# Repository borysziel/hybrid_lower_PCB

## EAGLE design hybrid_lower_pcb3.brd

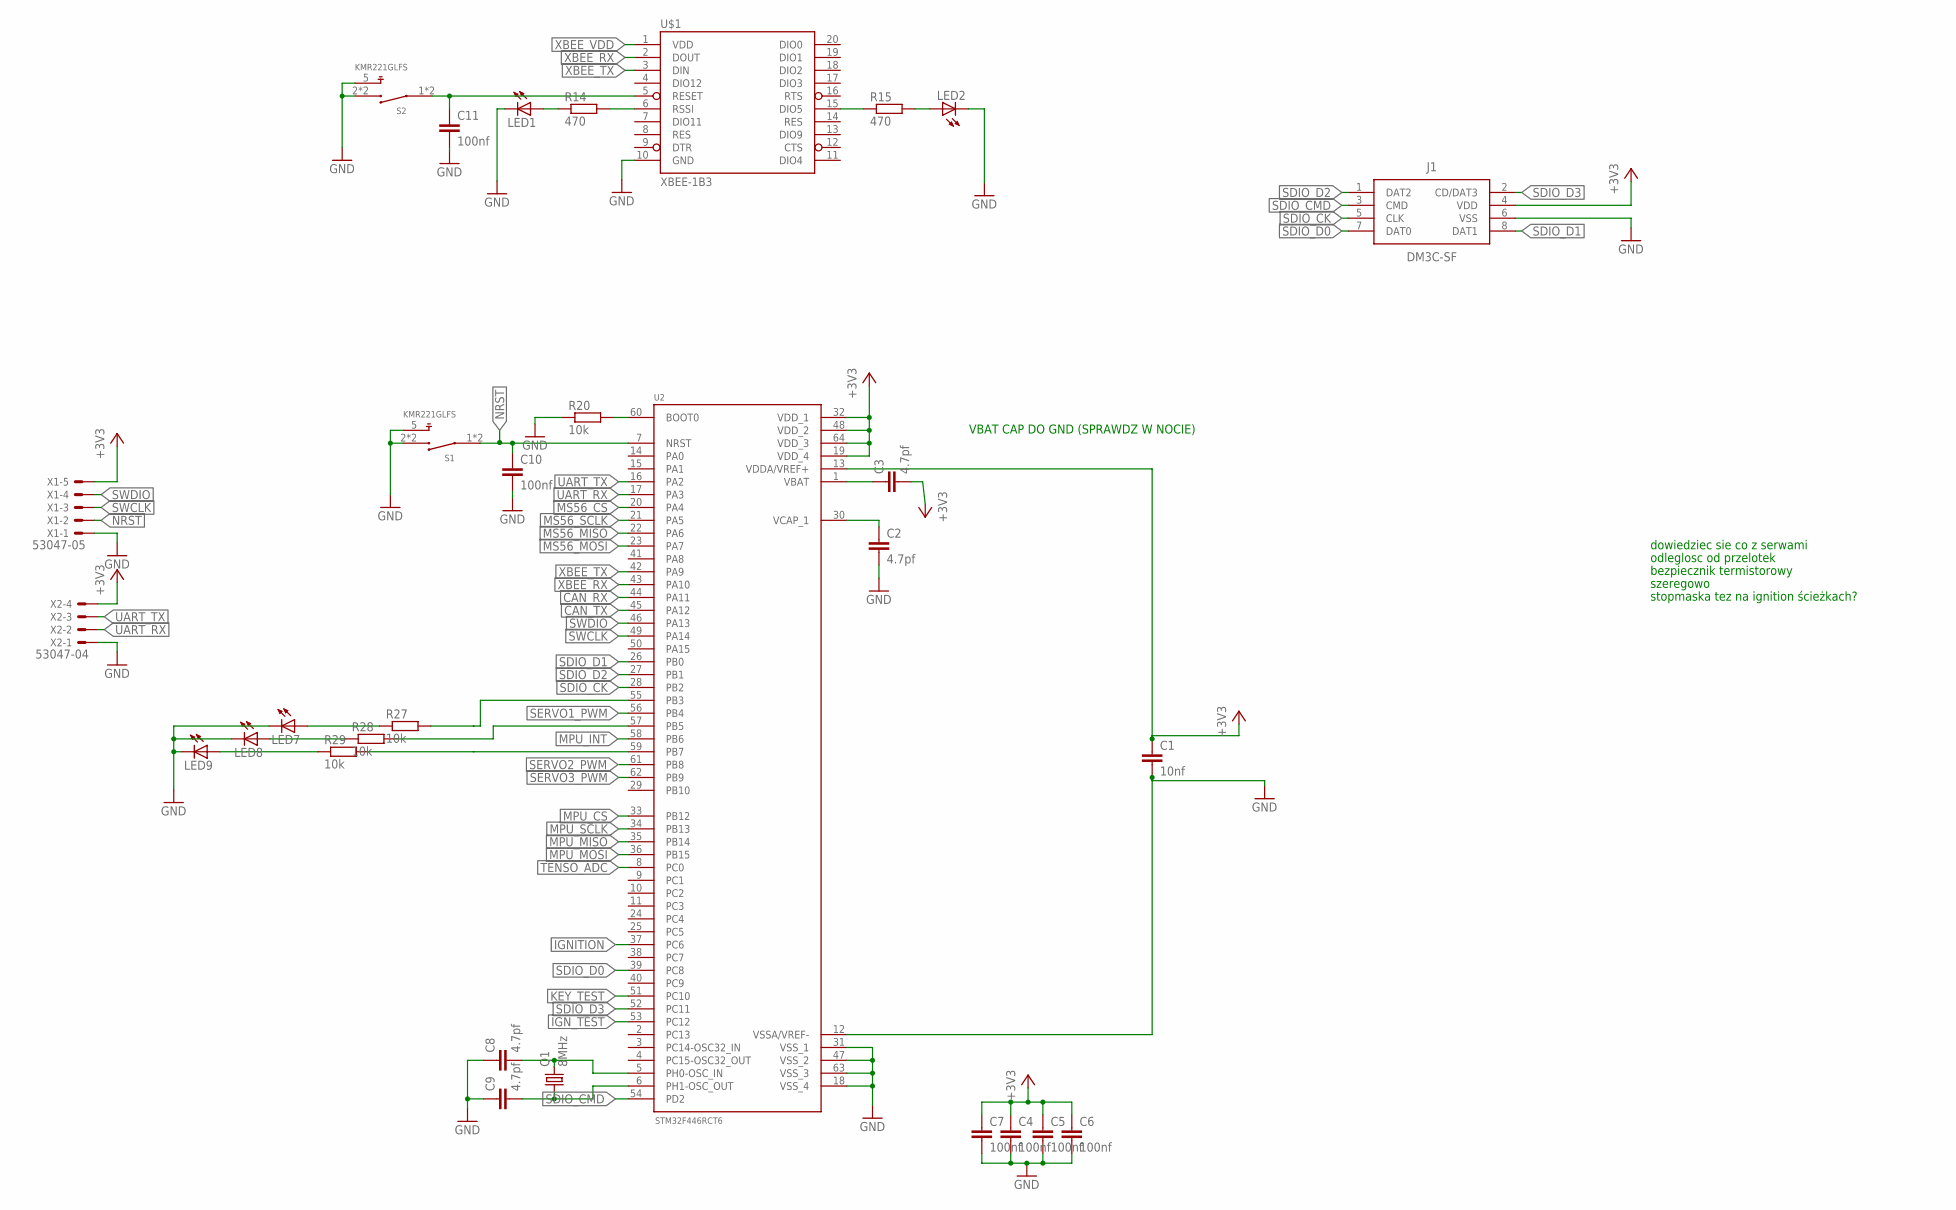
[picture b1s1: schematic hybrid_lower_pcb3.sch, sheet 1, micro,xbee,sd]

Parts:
C1: 10nf; C0603
C2, C3, C8, C9: 4.7pf; C0603
C4, C5, C6, C7, C10, C11: 100nf; C0603
J1: DM3C-SF
LED1, LED2, LED7, LED8, LED9: LED0603; LED-0603
Q1: 8MHz; CTS406
R14, R15: 470; R0603
R20, R27, R28, R29: 10k; R0603
S1, S2: KMR221GLFS; SW_KMR221GLFS
U2: STM32F446RCT6; QFP50P1200X1200X160-64N
U$1: XBEE-1B3; XBEE-SMD
X1: 53047-05
X2: 53047-04

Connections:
+3V3: C1.1, C3.2, C4.1, C5.1, C6.1, C7.1, J1.4 (VDD), U2.13 (VDDA/VREF+), U2.19 (VDD_4), U2.32 (VDD_1), U2.48 (VDD_2), U2.64 (VDD_3), X1.5, X2.4; also elsewhere on the board
CAN_RX: U2.44 (PA11); also elsewhere on the board
CAN_TX: U2.45 (PA12); also elsewhere on the board
DUPA: C11.1, S2.1, S2.4 (1), U$1.5 (RESET)
GND: C1.2, C2.2, C4.2, C5.2, C6.2, C7.2, C8.1, C9.1, C10.2, C11.2, J1.6 (VSS), LED1.C, LED2.C, LED7.C, LED8.C, LED9.C, R20.1, S1.2 (3), S1.3, S1.5, S2.2 (3), S2.3, S2.5, U2.12 (VSSA/VREF-), U2.18 (VSS_4), U2.31 (VSS_1), U2.47 (VSS_2), U2.63 (VSS_3), U$1.10 (GND), X1.1, X2.1; also elsewhere on the board
IGNITION: U2.37 (PC6); also elsewhere on the board
IGN_TEST: U2.53 (PC12); also elsewhere on the board
KEY_TEST: U2.51 (PC10); also elsewhere on the board
MPU_CS: U2.33 (PB12); also elsewhere on the board
MPU_INT: U2.58 (PB6); also elsewhere on the board
MPU_MISO: U2.35 (PB14); also elsewhere on the board
MPU_MOSI: U2.36 (PB15); also elsewhere on the board
MPU_SCLK: U2.34 (PB13); also elsewhere on the board
MS56_CS: U2.20 (PA4); also elsewhere on the board
MS56_MISO: U2.22 (PA6); also elsewhere on the board
MS56_MOSI: U2.23 (PA7); also elsewhere on the board
MS56_SCLK: U2.21 (PA5); also elsewhere on the board
unnamed: C2.1, U2.30 (VCAP_1)
unnamed: C3.1, U2.1 (VBAT)
unnamed: LED1.A, R14.1
unnamed: C8.2, Q1.3 (2), U2.5 (PH0-OSC_IN)
unnamed: C9.2, Q1.1, U2.6 (PH1-OSC_OUT)
unnamed: LED2.A, R15.2
unnamed: R14.2, U$1.6 (RSSI)
unnamed: R15.1, U$1.15 (DIO5)
unnamed: R20.2, U2.60 (BOOT0)
unnamed: R27.2, U2.55 (PB3)
unnamed: R28.2, U2.57 (PB5)
unnamed: R29.2, U2.59 (PB7)
unnamed: LED7.A, R27.1
unnamed: LED8.A, R28.1
unnamed: LED9.A, R29.1
NRST: C10.1, S1.1, S1.4 (1), U2.7 (NRST), X1.2
SDIO_CK: J1.5 (CLK), U2.28 (PB2)
SDIO_CMD: J1.3 (CMD), U2.54 (PD2)
SDIO_D0: J1.7 (DAT0), U2.39 (PC8)
SDIO_D1: J1.8 (DAT1), U2.26 (PB0)
SDIO_D2: J1.1 (DAT2), U2.27 (PB1)
SDIO_D3: J1.2 (CD/DAT3), U2.52 (PC11)
SERVO1_PWM: U2.56 (PB4)
SERVO2_PWM: U2.61 (PB8); also elsewhere on the board
SERVO3_PWM: U2.62 (PB9); also elsewhere on the board
SWCLK: U2.49 (PA14), X1.3
SWDIO: U2.46 (PA13), X1.4
TENSO_ADC: U2.8 (PC0); also elsewhere on the board
UART_RX: U2.17 (PA3), X2.2
UART_TX: U2.16 (PA2), X2.3
XBEE_RX: U2.43 (PA10), U$1.2 (DOUT)
XBEE_TX: U2.42 (PA9), U$1.3 (DIN)
XBEE_VDD: U$1.1 (VDD); also elsewhere on the board

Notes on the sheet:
dowiedziec sie co z serwami
odleglosc od przelotek
bezpiecznik termistorowy
szeregowo
stopmaska tez na ignition ścieżkach?
VBAT CAP DO GND (SPRAWDZ W NOCIE)

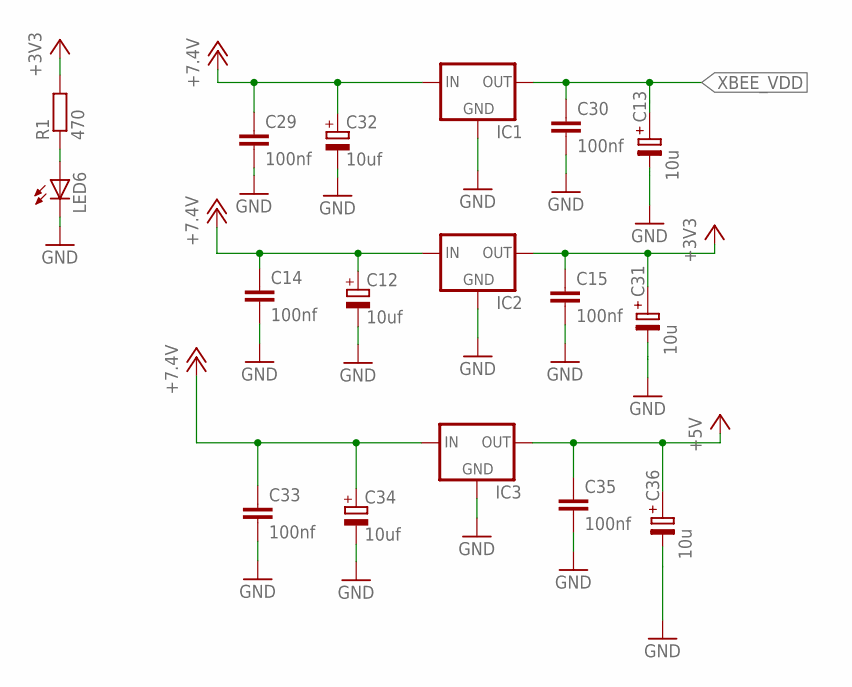
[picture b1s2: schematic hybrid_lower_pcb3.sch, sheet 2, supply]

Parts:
C12, C32, C34: 10uf; SANYO-OSCON_SMD_B6
C13, C31, C36: 10u; TE-B-3528
C14, C15, C29, C30, C33, C35: 100nf; C0603
IC1, IC2, IC3: LM1117; SOT223
LED6: LED0603; LED-0603
R1: 470; R0603

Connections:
+3V3: C15.1, C31.+, IC2.2 (OUT), R1.2; also elsewhere on the board
+5V: C35.1, C36.+, IC3.2 (OUT); also elsewhere on the board
+12V: C12.+, C14.1, C29.1, C32.+, C33.1, C34.+, IC1.3 (IN), IC2.3 (IN), IC3.3 (IN); also elsewhere on the board
GND: C12.-, C13.-, C14.2, C15.2, C29.2, C30.2, C31.-, C32.-, C33.2, C34.-, C35.2, C36.-, IC1.1 (GND), IC2.1 (GND), IC3.1 (GND), LED6.C; also elsewhere on the board
unnamed: LED6.A, R1.1
XBEE_VDD: C13.+, C30.1, IC1.2 (OUT); also elsewhere on the board

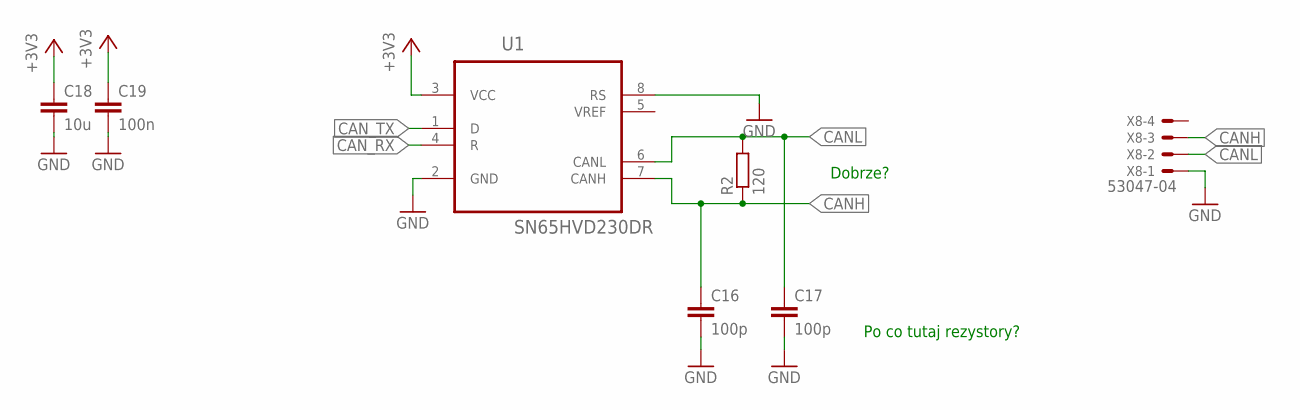
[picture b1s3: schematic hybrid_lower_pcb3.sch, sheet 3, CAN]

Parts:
C16, C17: 100p; C0603
C18: 10u; C0603
C19: 100n; C0603
R2: 120; R0603
U1: SN65HVD230DR; SOIC127P600X175-8N
X8: 53047-04

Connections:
+3V3: C18.1, C19.1, U1.3 (VCC); also elsewhere on the board
CANH: C16.1, R2.1, U1.7 (CANH), X8.3; also elsewhere on the board
CANL: C17.1, R2.2, U1.6 (CANL), X8.2; also elsewhere on the board
CAN_RX: U1.4 (R); also elsewhere on the board
CAN_TX: U1.1 (D); also elsewhere on the board
GND: C16.2, C17.2, C18.2, C19.2, U1.2 (GND), U1.8 (RS), X8.1; also elsewhere on the board

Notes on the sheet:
Po co tutaj rezystory?
Dobrze?

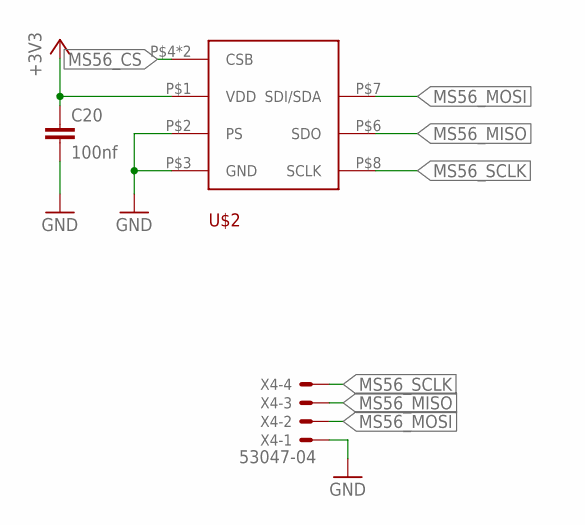
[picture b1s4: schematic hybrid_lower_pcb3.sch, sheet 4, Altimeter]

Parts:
C20: 100nf; C0603
U$2: MS56XX
X4: 53047-04

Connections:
+3V3: C20.1, U$2.P$1 (VDD); also elsewhere on the board
GND: C20.2, U$2.P$2 (PS), U$2.P$3 (GND), X4.1; also elsewhere on the board
MS56_CS: U$2.P$4 (CSB), U$2.P$5 (CSB); also elsewhere on the board
MS56_MISO: U$2.P$6 (SDO), X4.3; also elsewhere on the board
MS56_MOSI: U$2.P$7 (SDI/SDA), X4.2; also elsewhere on the board
MS56_SCLK: U$2.P$8 (SCLK), X4.4; also elsewhere on the board

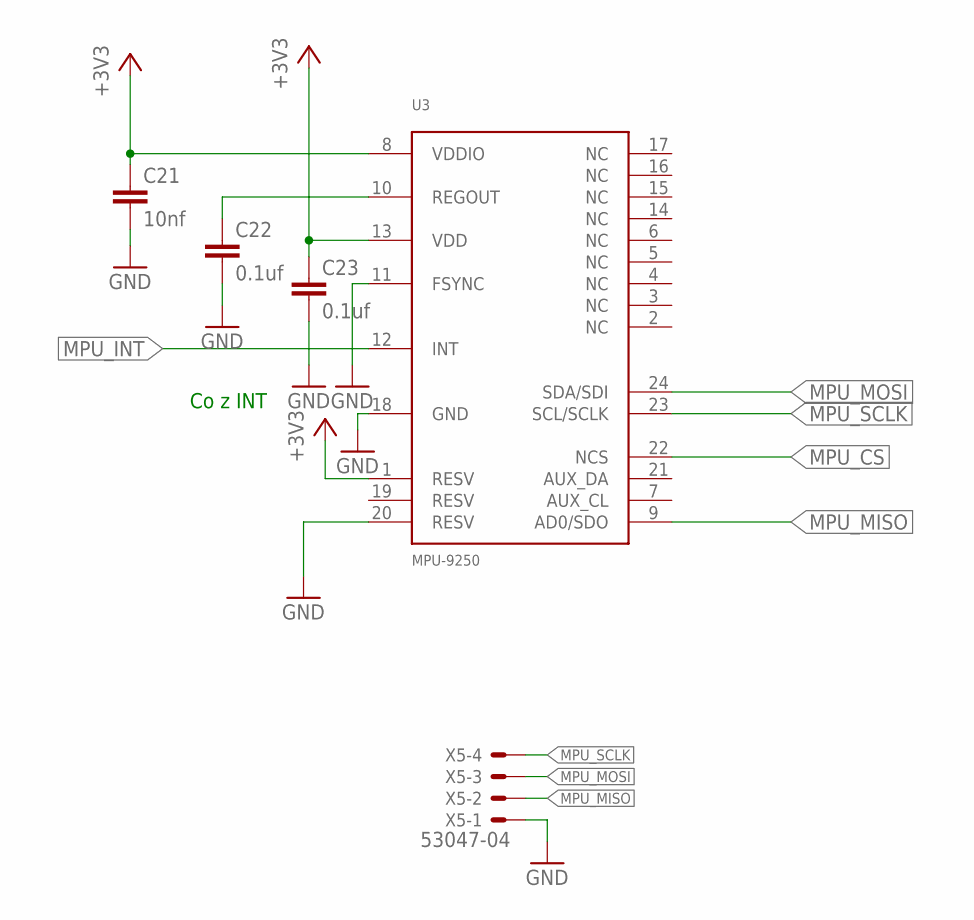
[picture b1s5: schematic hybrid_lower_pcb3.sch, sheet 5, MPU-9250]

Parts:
C21: 10nf; C0603
C22, C23: 0.1uf; C0603
U3: MPU-9250
X5: 53047-04

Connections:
+3V3: C21.1, C23.1, U3.1 (RESV), U3.8 (VDDIO), U3.13 (VDD); also elsewhere on the board
GND: C21.2, C22.2, C23.2, U3.11 (FSYNC), U3.18 (GND), U3.20 (RESV), X5.1; also elsewhere on the board
MPU_CS: U3.22 (NCS); also elsewhere on the board
MPU_INT: U3.12 (INT); also elsewhere on the board
MPU_MISO: U3.9 (AD0/SDO), X5.2; also elsewhere on the board
MPU_MOSI: U3.24 (SDA/SDI), X5.3; also elsewhere on the board
MPU_SCLK: U3.23 (SCL/SCLK), X5.4; also elsewhere on the board
unnamed: C22.1, U3.10 (REGOUT)

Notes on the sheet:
Co z INT

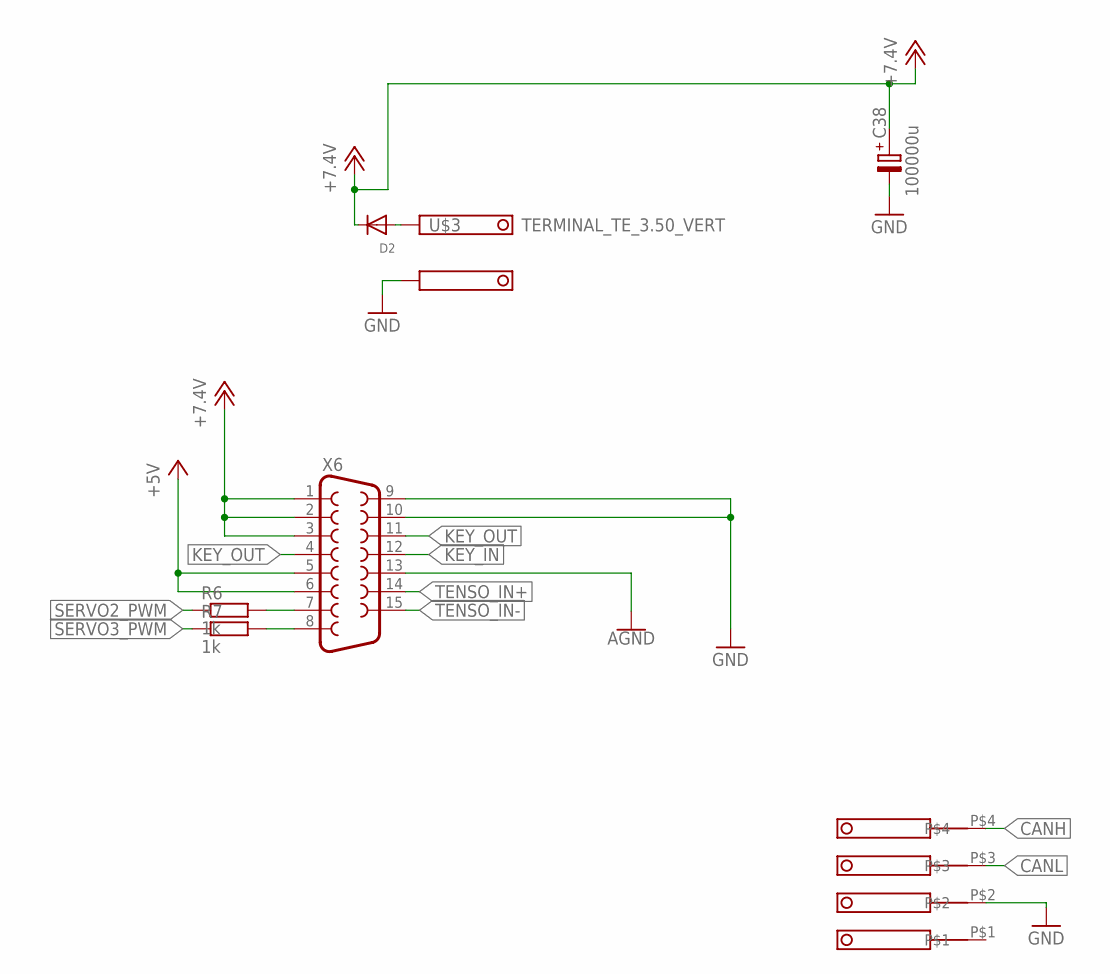
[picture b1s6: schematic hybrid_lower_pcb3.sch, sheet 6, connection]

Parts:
C38: 100000u; TE-B-3528
D2: DIODESOD-523; SOD-523
R6, R7: 1k; R0603
U$3: TERMINAL_TE_3.50_VERT; TE_3.5_TERMINAL_VERT
U$10: 39505-1005
X6: F15VP

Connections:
+5V: X6.5, X6.6; also elsewhere on the board
+12V: C38.+, D2.K (C), X6.1, X6.2, X6.3; also elsewhere on the board
AGND: X6.13; also elsewhere on the board
CANH: U$10.P$4; also elsewhere on the board
CANL: U$10.P$3; also elsewhere on the board
GND: C38.-, U$3.P$2 (K1), U$10.P$2, X6.9, X6.10; also elsewhere on the board
KEY_IN: X6.12; also elsewhere on the board
KEY_OUT: X6.4, X6.11; also elsewhere on the board
unnamed: R6.2, X6.7
unnamed: R7.2, X6.8
unnamed: D2.A, U$3.P$1 (K)
SERVO2_PWM: R6.1; also elsewhere on the board
SERVO3_PWM: R7.1; also elsewhere on the board
TENSO_IN+: X6.14; also elsewhere on the board
TENSO_IN-: X6.15; also elsewhere on the board

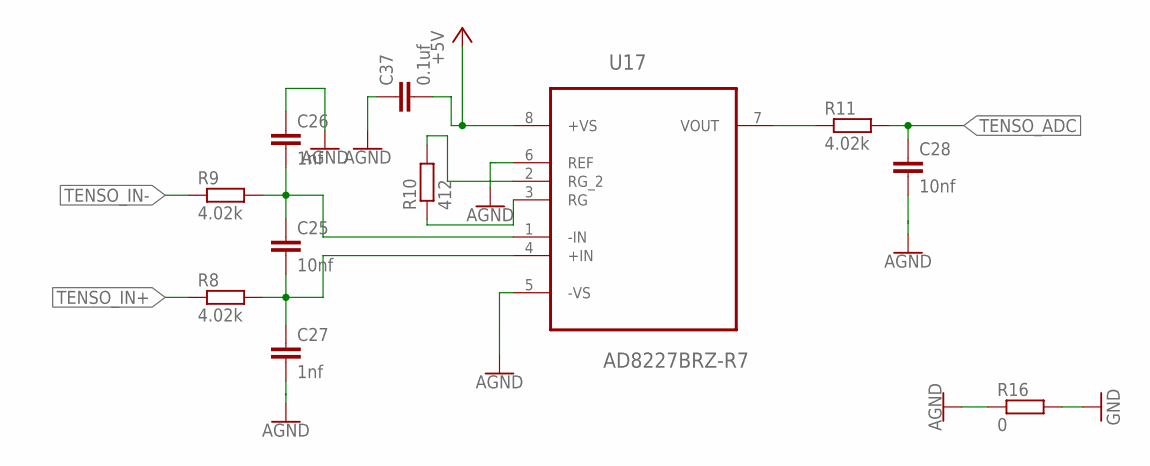
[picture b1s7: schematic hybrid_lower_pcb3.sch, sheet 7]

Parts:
C25, C28: 10nf; C0603
C26, C27: 1nf; C0603
C37: 0.1uf; C0603
R8, R9, R11: 4.02k; R0603
R10: 412; R0805
R16: 0; R0603
U17: AD8227BRZ-R7; SOIC127P600X175-8N

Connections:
+5V: C37.2, U17.8 (+VS); also elsewhere on the board
AGND: C26.1, C27.2, C28.2, C37.1, R16.1, U17.5 (-VS), U17.6 (REF); also elsewhere on the board
GND: R16.2; also elsewhere on the board
unnamed: C25.1, C26.2, R9.2, U17.1 (-IN)
unnamed: C25.2, C27.1, R8.2, U17.4 (+IN)
unnamed: R10.1, U17.3 (RG)
unnamed: R10.2, U17.2 (RG_2)
unnamed: R11.1, U17.7 (VOUT)
TENSO_ADC: C28.1, R11.2; also elsewhere on the board
TENSO_IN+: R8.1; also elsewhere on the board
TENSO_IN-: R9.1; also elsewhere on the board

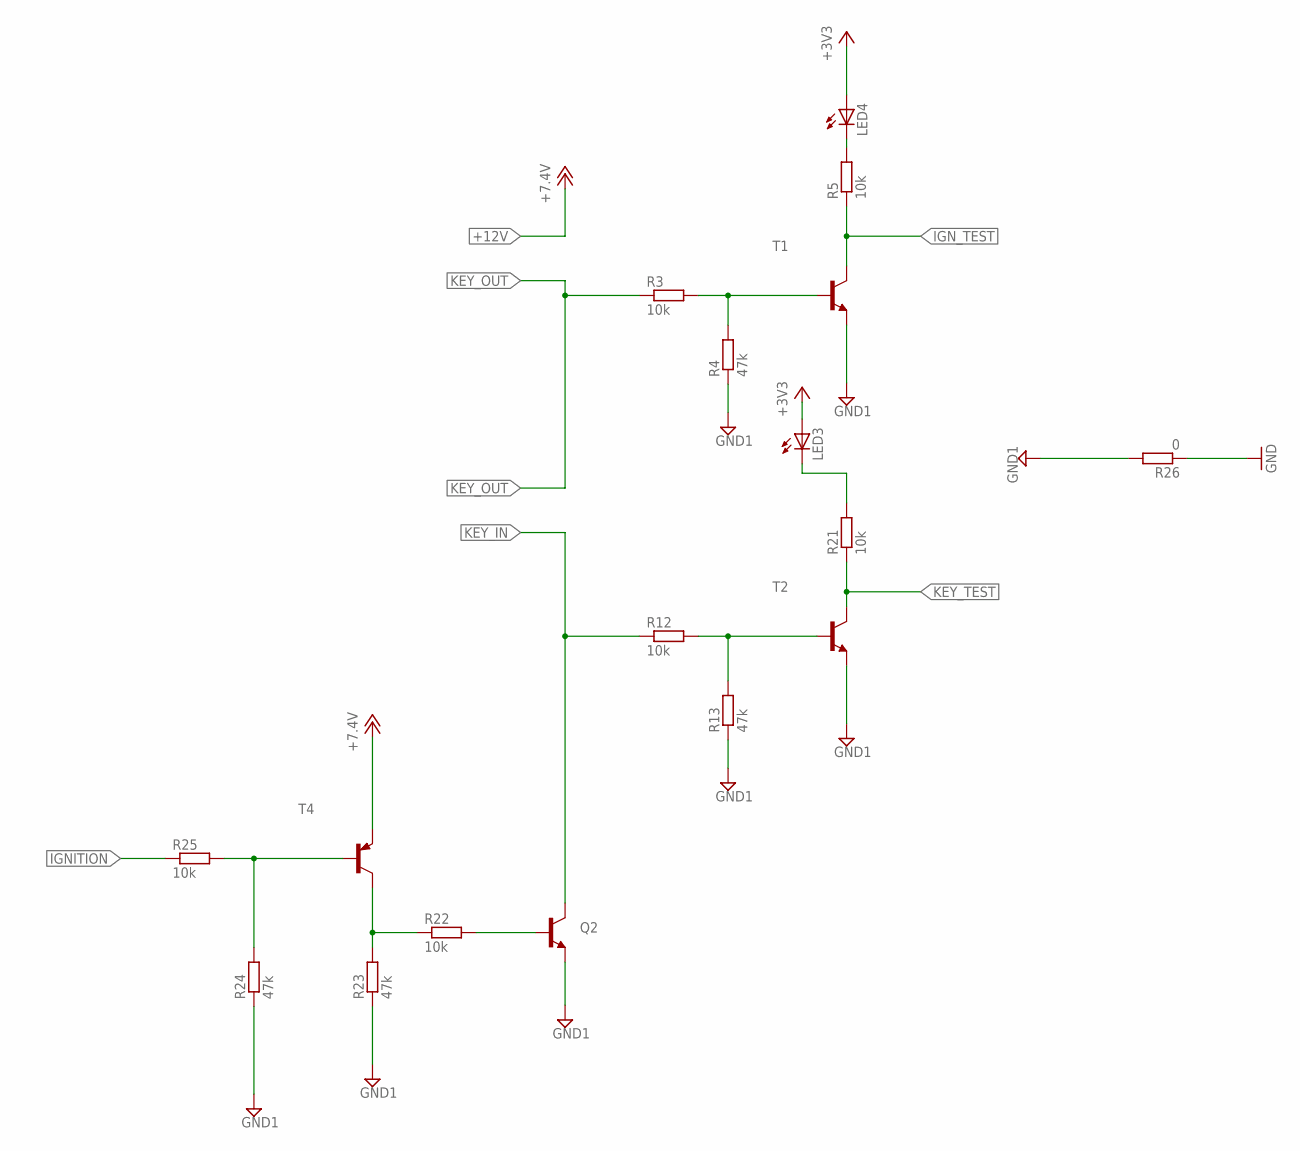
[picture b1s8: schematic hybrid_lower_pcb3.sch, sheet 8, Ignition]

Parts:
LED3, LED4: LED0603; LED-0603
Q2: TRANSISTOR_NPNSOT23-3; SOT23-3
R3, R5, R12, R21, R22, R25: 10k; R0603
R4, R13, R23, R24: 47k; R0603
R26: 0; R0603
T1, T2: BCW81-NPN-SOT23-BEC; SOT23-BEC
T4: BC807-16-PNP-SOT23-BEC; SOT23-BEC

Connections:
+3V3: LED3.A, LED4.A; also elsewhere on the board
+12V: T4.E; also elsewhere on the board
GND: R26.1; also elsewhere on the board
GND1: Q2.2 (E), R4.1, R13.1, R23.1, R24.1, R26.2, T1.E, T2.E
IGNITION: R25.1; also elsewhere on the board
IGN_TEST: R5.1, T1.C; also elsewhere on the board
KEY_IN: Q2.3 (C), R12.1; also elsewhere on the board
KEY_OUT: R3.1; also elsewhere on the board
KEY_TEST: R21.1, T2.C; also elsewhere on the board
unnamed: R3.2, R4.2, T1.B
unnamed: R12.2, R13.2, T2.B
unnamed: LED4.C, R5.2
unnamed: LED3.C, R21.2
unnamed: Q2.1 (B), R22.2
unnamed: R22.1, R23.2, T4.C
unnamed: R24.2, R25.2, T4.B

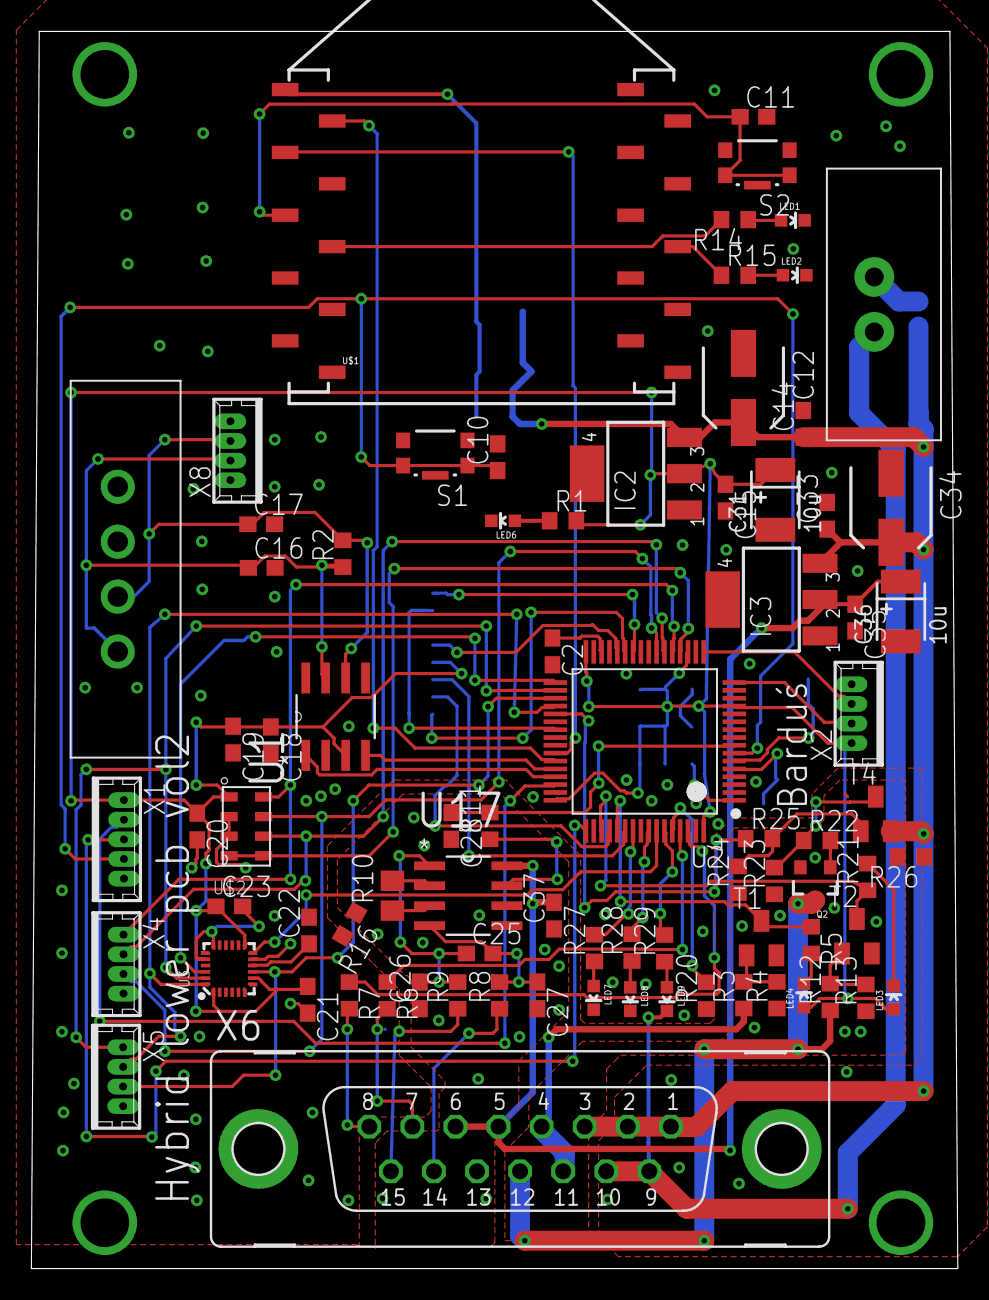
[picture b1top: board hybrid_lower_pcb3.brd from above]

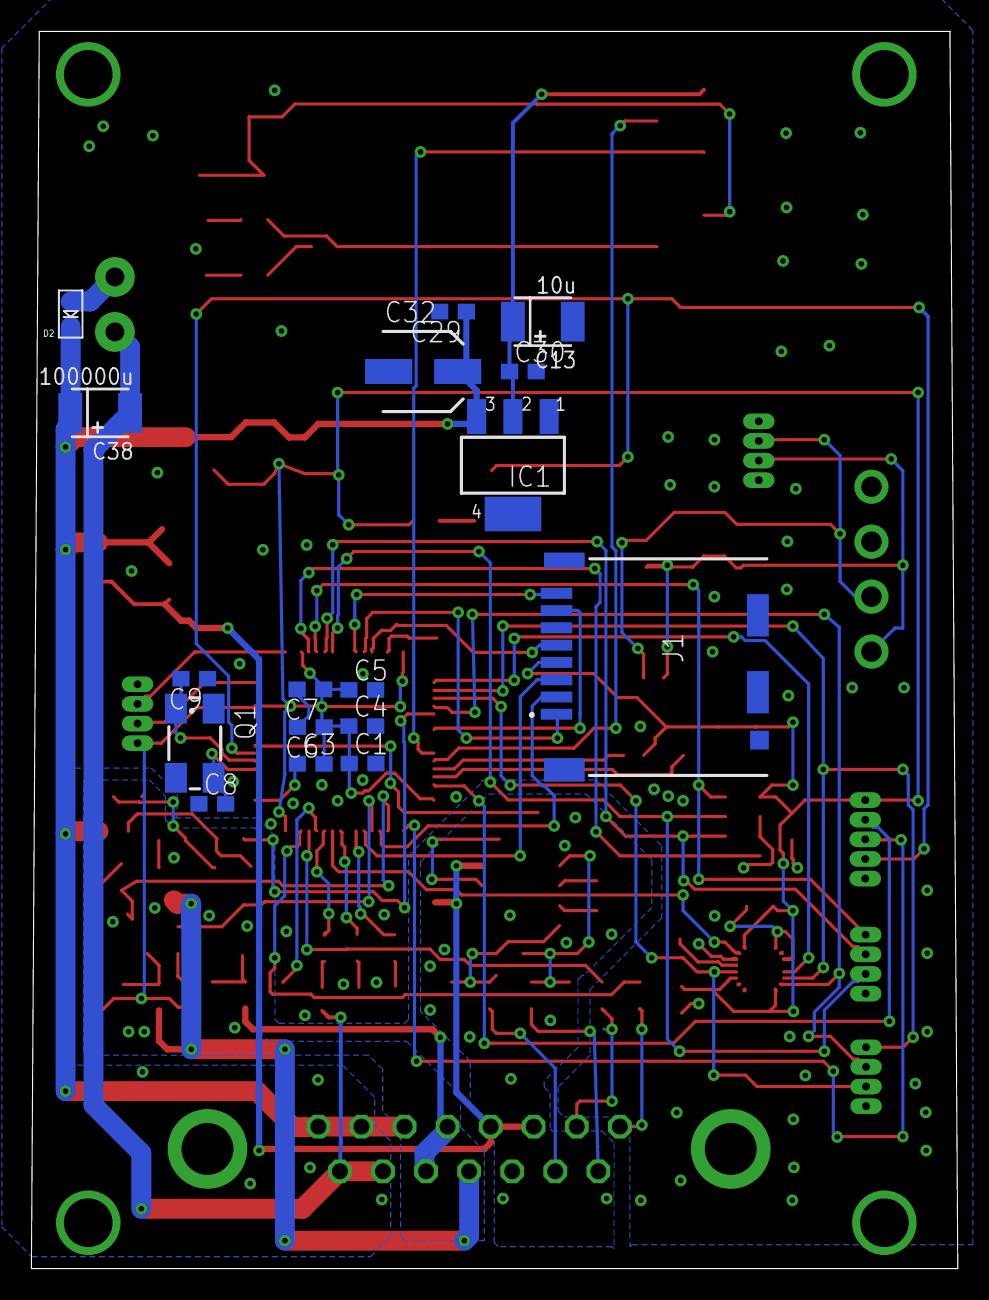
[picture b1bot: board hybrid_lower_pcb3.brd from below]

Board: 2 copper layers, 59.0 x 78.8 mm, 98 parts (17 on the bottom side), 76 nets.

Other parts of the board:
U$15: LOGO

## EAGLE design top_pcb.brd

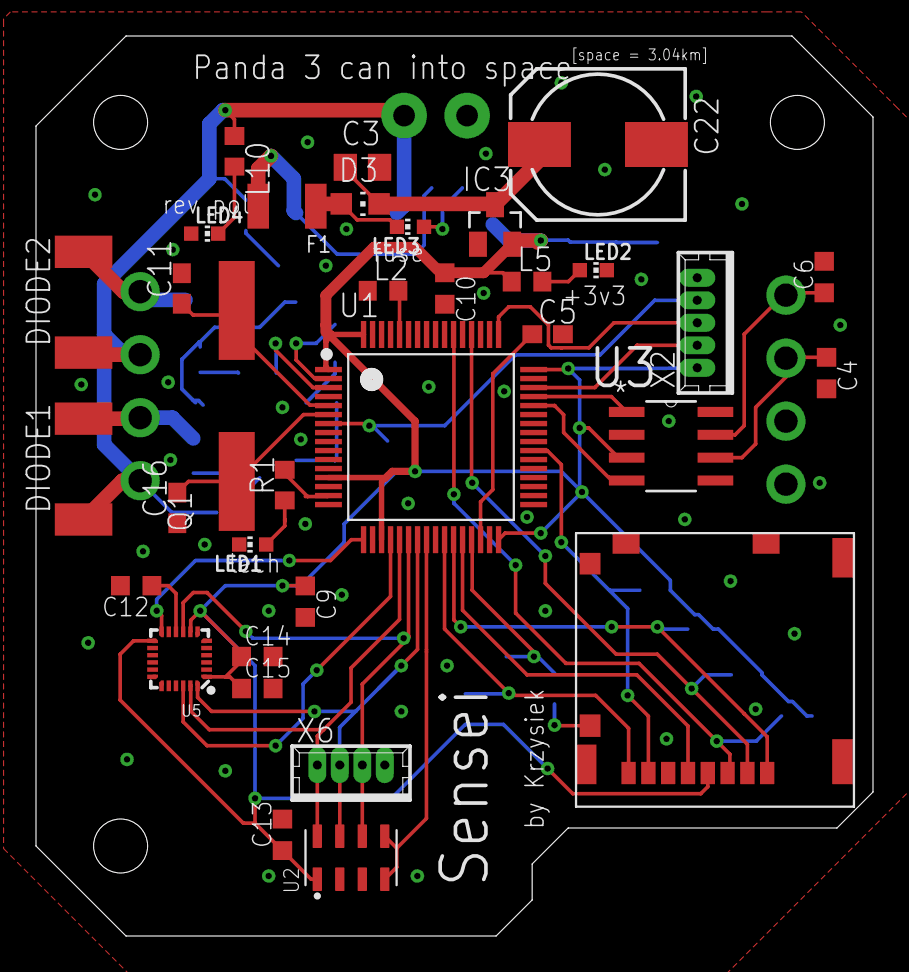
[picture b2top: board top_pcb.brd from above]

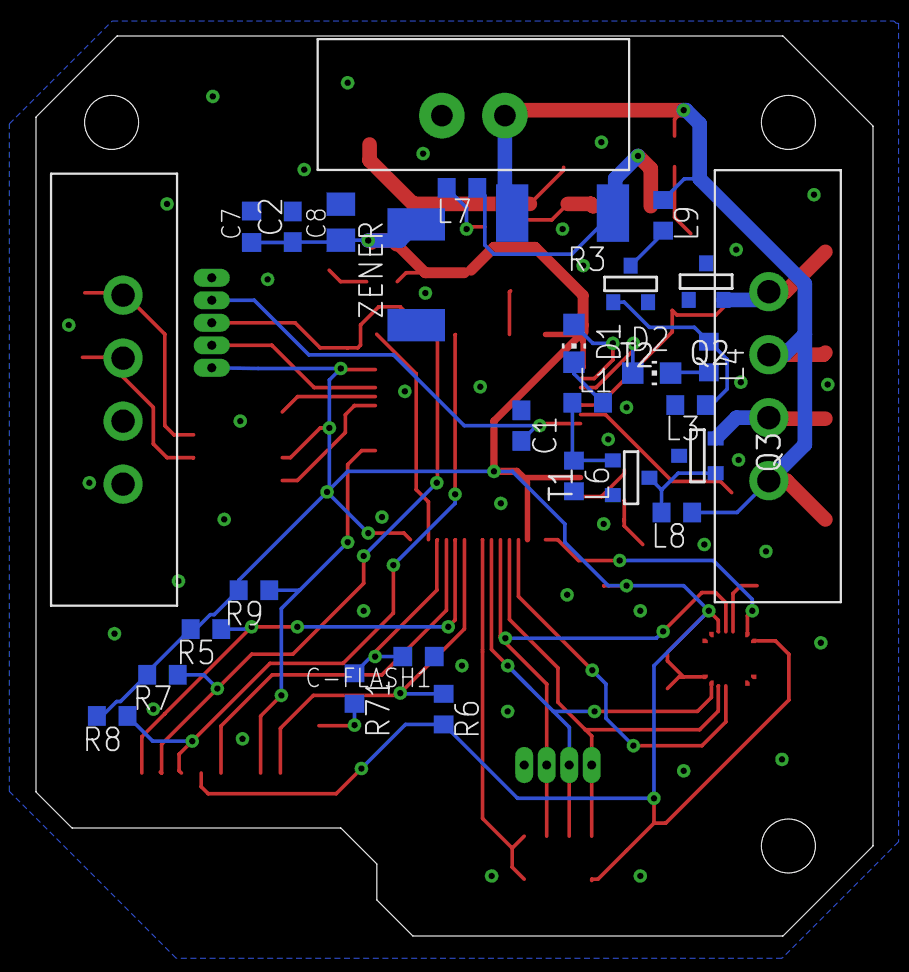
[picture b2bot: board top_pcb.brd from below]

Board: 2 copper layers, 46.5 x 50.0 mm, 63 parts (29 on the bottom side), 47 nets.

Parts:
C1: 0.1u; C0603
C2: 2u2; C0603
C3: 4u7; C0805
C4, C6, C13: 100p; C0603K
C5: 4.7u; C0603
C7, C9, C10: 100n; C0603K
C8: 10u; C0805K
C11, C16: 30pF; C0603
C12, C15: H100n; C0603K
C14: H10n; C0603K
C22: 10u; 140CLH-0810
C-FLASH1: 100n; C0603K
D1, D2, D3: CHIP-LED0805
DIODE1, DIODE2: R2512
F1: SMD-PPTC-750MA-6V(1210); F1210
IC3: MCP1703CB; SOT23
L1, L4: 5k; R0603
L2: 470; R0603
L3, L6, L8, L9: 100k; R0603
L5, L7: 2.3k; R0603
L10: 1k; R0603
LED1, LED2, LED3, LED4: CHIP-LED0603
Q1: 8MHz; CSM-7X-DU
Q2, Q3: SOT-23
R1: 470R; R0603
R3: R2512
R5, R6, R7, R8, R9: 47k; R0603
R71: 2k; R0603
T1, T2: SOT-23
U1: STM32F446RCT6; QFP50P1200X1200X160-64N
U2: MS561101BA03-00; SON125P500X300X100-8N
U3: SN65HVD230DR; SOIC127P600X175-8N
U5: MPU-9250
U$1, U$10: 39505-1005
U$2: TERMINAL_TE_3.50_VERT; TE_3.5_TERMINAL_VERT
U$4: MOLEX_MICRO_SD_503182-1853
X2: 53047-05
X6: 53047-04
ZENER: R2512

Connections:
+3V3: C2.1, C7.1, C8.1, C9.1, C10.1, C13.1, C14.1, C15.1, IC3.2, L5.1, R5.2, R6.2, R7.2, R8.2, R9.2, U1.1, U1.13, U1.19, U1.32, U1.48, U1.64, U2.1, U3.3, U5.1, U5.8, U5.13, U$4.PIN4, X2.5, ZENER.2
BATTERY: DIODE1.1, DIODE2.1, L8.1, L9.1, L10.1, R3.2, U$1.P$2, U$1.P$4, U$2.P$2
CAN1_RX: U1.44, U3.4
CAN1_TX: U1.45, U3.1
CANH: C6.1, U3.7, U$10.P$4
CANL: C4.1, U3.6, U$10.P$3
GND: C1.1, C2.2, C3.2, C4.2, C5.2, C6.2, C7.2, C8.2, C9.2, C10.2, C11.2, C12.2, C13.2, C14.2, C15.2, C16.1, C22.-, C-FLASH1.1, IC3.1, L2.1, L3.2, L6.2, LED1.C, LED2.C, LED4.A, Q2.1, Q3.1, T1.2, T2.2, U1.12, U1.18, U1.31, U1.47, U1.63, U2.2, U2.3, U3.2, U3.8, U5.11, U5.18, U5.20, U$2.P$1, U$4.DETECT_GND, U$4.PIN6, U$10.P$2, X2.1, X6.1, ZENER.1
IGNITE1: D1.A, U1.2
IGNITE2: D2.A, U1.3
IN: C11.1, Q1.2, U1.5
LED_ON: R1.2, U1.15
MPU_CS: U1.20, U5.22
MPU_INT: U1.17, U5.12
MS_CS: U1.24, U2.4, U2.5
unnamed: C5.1, U1.30
unnamed: L7.2, LED3.A
unnamed: L3.1, L4.1, T2.3
unnamed: L5.2, LED2.A
unnamed: LED1.A, R1.1
unnamed: D1.C, L1.2
unnamed: L1.1, L6.1, T1.3
unnamed: F1.2, L7.1, R3.1
unnamed: L10.2, LED4.C
unnamed: L2.2, U1.60
unnamed: D3.A, F1.1, LED3.C
unnamed: C12.1, U5.10
unnamed: L8.2, Q3.3, T1.1
unnamed: D2.C, L4.2
unnamed: L9.2, T2.1
unnamed: R71.2, U$4.DETECT
NRST: C1.2, U1.7, X2.2
OUT: C16.2, Q1.1, U1.6
OUT1: DIODE1.2, Q3.2, U$1.P$3
OUT2: DIODE2.2, Q2.2, U$1.P$1
SAFE_BAT: C3.1, C22.+, D3.C, IC3.3
SDIO_CLK: U1.28, U$4.PIN5
SDIO_CMD: R8.1, U1.54, U$4.PIN3
SDIO_D0: R9.1, U1.39, U$4.PIN7
SDIO_D1: R6.1, U1.26, U$4.PIN8
SDIO_D2: R5.1, U1.27, U$4.PIN1
SDIO_D3: R7.1, U1.52, U$4.PIN2
SD_DETECT: C-FLASH1.2, R71.1, U1.29
SPI1_MISO: U1.22, U2.6, U5.9, X6.2
SPI1_MOSI: U1.23, U2.7, U5.24, X6.3
SPI1_SCK: U1.21, U2.8, U5.23, X6.4
SWCLK: U1.49, X2.3
SWDIO: U1.46, X2.4

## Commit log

2019-08-27 last version

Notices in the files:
parts and their libraries:
SparkFun: Licensing: CC v3.0 Share-Alike You are welcome to use this library for commercial purposes.
capacitors: Copyright (C) 2004, Bob Starr
SparkFun-PowerSymbols: Licensing: Creative Commons ShareAlike 4.0 International - https://creativecommons.org/licenses/by-sa/4.0
